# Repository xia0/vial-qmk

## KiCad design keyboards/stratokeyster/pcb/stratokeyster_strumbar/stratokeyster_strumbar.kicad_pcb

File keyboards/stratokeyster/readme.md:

# stratokeyster

## bom
|item|qty|
|---|---|
|M3 x 10~12 mm bolt*|16|
|M3 x 30 mm bolt*|4|
|M3 x 80 mm bolt|3|
|M3 nyloc nut|3|
|M3 heat set insert 5 mm OD x 4~5 mm L|20|
|M3 washer#|0~8|
|ec11 rotary encoder 15 mm half shaft|1|
|rs26 3 pole 4 throw rotary switch 15 mm half shaft|1|
|5 way pickup selector|1|
|passive buzzer 6.5 mm pin spacing|1|
|18 pin 2.54 mm pitch angled connector male^|1|
|18 pin 2.54 mm pitch dupont cable female end ~5 cm^|1|
|usb breakout board male|1|
|usb breakout board female|1|
|mx switch for fretboard|39-40|
|mx switch for bridge†|1|
|mx switch for strumbars†|6|
|2u pcb mount stab|2-3|
|2u plate mount stab|1|
|raspberry pi pico|1|
|fretboard pcb|1|
|fretboard plate|1|
|strumbar pcb|1|
|3d printed parts||

_\* phillips head silver colour bolts recommended for aesthetic reasons_\
_^ alternatively, a combination of pins that add up to 18_\
_# for tuning strum bar clearance. you could also use a 3d printed washer, bits of paper, etc..._\
_† heavy and clicky recommended e.g. kailh box navy or kailh box black_

## pick guard wiring
#### pickup selector
- com (4 or 5) -> row 3
- 1 or 6 -> col 8
- 2 or 7 -> col 7
- 3 or 8 -> col 6

#### EC11 rotary encoder
- push button -> row 3, col 9
- encoder -> encA, gnd, encB

encoder direction can be changed later on config layer

#### RS26 rotary switch
- A -> row 3
- 1 -> col 13
- 2 -> col 12
- 3 -> col 11
- 4 -> col 10

#### bridge key
row 1, col 13

#### buzzer
- +ve -> GP0
- -ve -> ground

#### free pin
row 2, col 13

## usage
#### pickup selector (mods) defaults
| neck | neck + mid | middle | bridge + mid | bridge |
|---|---|---|---|---|
| gui | ctrl + alt | alt | ctrl | none |

#### rotary encoder
- volume control
- mute/unmute

#### rotary switch
| pos 1 (ccw) | pos 2 | pos 3 | pos 4 (cw) |
|---|---|---|---|
| config | normal typing | strum typing | numbers |

#### bridge switch (palm mute)
does not hold down the key and does not register space if the key is released before the strum bar.

### config layer
the hid console in qmk toolbox can be useful to view which options are set but is not necessary.
|control|function|
|---|---|
|middle strum bar|toggle between simple mode and normal mode*|
|backslash|toggle between backslash or backspace|
|tab|toggle between tab or escape|
|bridge key|NUM layer replaces palm mute (quick access to high strings)|
|encoder push button|bootloader|
|encoder rotate|set direction of rotation as clockwise|
|a|toggle audio|
|d|toggle drop D tuning|
|r|reset eeprom|
|[|???|

_* in simple mode, only the middle strum bar is active._

#### edit mods
mods can be changed by selecting the pickup position, hold the desired mods and press enter to set.
|left shift|z|x|c|
|---|---|---|---|
|left shift|left ctrl|left gui|left alt|

switch off the config layer to save to eeprom.

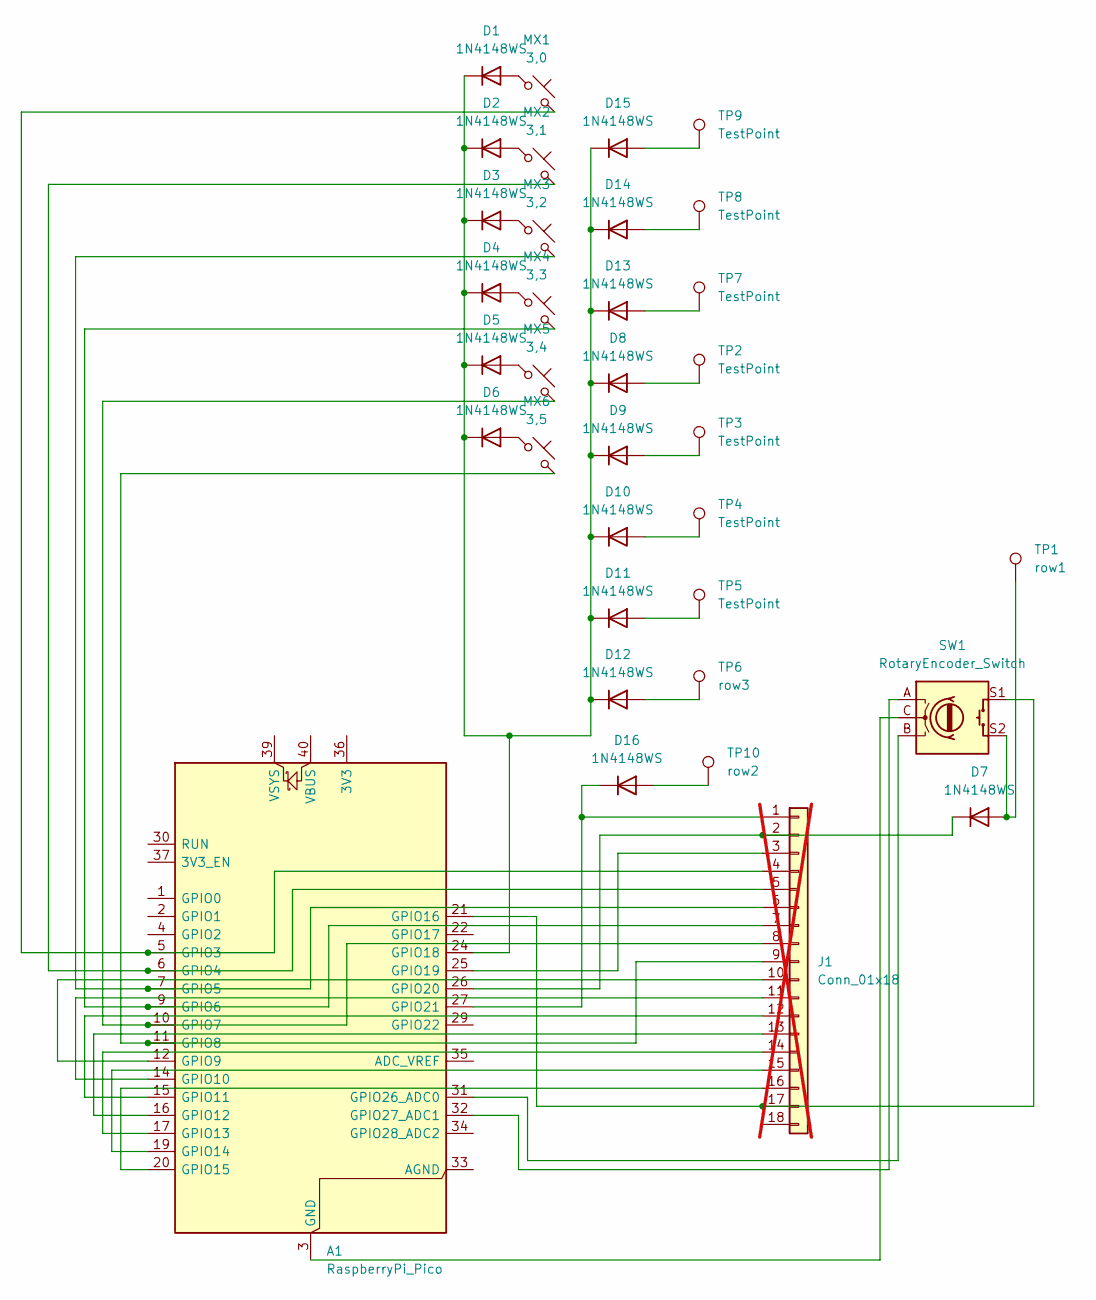
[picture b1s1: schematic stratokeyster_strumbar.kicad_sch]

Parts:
A1: RaspberryPi_Pico; RaspberryPi_Pico_Common_Unspecified
D1, D2, D3, D4, D5, D6, D7, D8, D9, D10, D11, D12, D13, D14, D15, D16: 1N4148WS; D_SOD-323_HandSoldering
J1: Conn_01x18; PinHeader_1x18_P2.54mm_Vertical; not fitted
MX1: 3,0; SW_MX_1u
MX2: 3,1; SW_MX_1u
MX3: 3,2; SW_MX_1u
MX4: 3,3; SW_MX_1u
MX5: 3,4; SW_MX_1u
MX6: 3,5; SW_MX_1u
SW1: RotaryEncoder_Switch
TP1: row1; TestPoint_Pad_1.5x1.5mm
TP2, TP3, TP4, TP5, TP7, TP8, TP9: TestPoint; TestPoint_Pad_1.5x1.5mm
TP6: row3; TestPoint_Pad_1.5x1.5mm
TP10: row2; TestPoint_Pad_1.5x1.5mm

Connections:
unnamed: A1.3 (GND), A1.8 (GND), A1.13 (GND), A1.18 (GND), A1.23 (GND), A1.28 (GND), A1.38 (GND), SW1.C
unnamed: A1.5 (GPIO3), J1.4, MX1.2
unnamed: A1.6 (GPIO4), J1.5, MX2.2
unnamed: A1.7 (GPIO5), J1.6, MX3.2
unnamed: A1.9 (GPIO6), J1.7, MX4.2
unnamed: A1.10 (GPIO7), J1.8, MX5.2
unnamed: A1.11 (GPIO8), J1.9, MX6.2
unnamed: A1.12 (GPIO9), J1.10
unnamed: A1.14 (GPIO10), J1.11
unnamed: A1.15 (GPIO11), J1.12
unnamed: A1.16 (GPIO12), J1.13
unnamed: A1.17 (GPIO13), J1.14
unnamed: A1.19 (GPIO14), J1.15
unnamed: A1.20 (GPIO15), J1.16
unnamed: A1.21 (GPIO16), J1.17, SW1.S1
unnamed: A1.24 (GPIO18), D1.1 (K), D2.1 (K), D3.1 (K), D4.1 (K), D5.1 (K), D6.1 (K), D8.1 (K), D9.1 (K), D10.1 (K), D11.1 (K), D12.1 (K), D13.1 (K), D14.1 (K), D15.1 (K)
unnamed: A1.25 (GPIO19), J1.3
unnamed: A1.26 (GPIO20), D7.1 (K), J1.2
unnamed: A1.27 (GPIO21), D16.1 (K), J1.1
unnamed: A1.31 (GPIO26_ADC0), SW1.B
unnamed: A1.32 (GPIO27_ADC1), SW1.A
unnamed: D1.2 (A), MX1.1
unnamed: D2.2 (A), MX2.1
unnamed: D3.2 (A), MX3.1
unnamed: D4.2 (A), MX4.1
unnamed: D5.2 (A), MX5.1
unnamed: D6.2 (A), MX6.1
unnamed: D7.2 (A), SW1.S2, TP1.1
unnamed: D8.2 (A), TP2.1
unnamed: D9.2 (A), TP3.1
unnamed: D10.2 (A), TP4.1
unnamed: D11.2 (A), TP5.1
unnamed: D12.2 (A), TP6.1
unnamed: D13.2 (A), TP7.1
unnamed: D14.2 (A), TP8.1
unnamed: D15.2 (A), TP9.1
unnamed: D16.2 (A), TP10.1

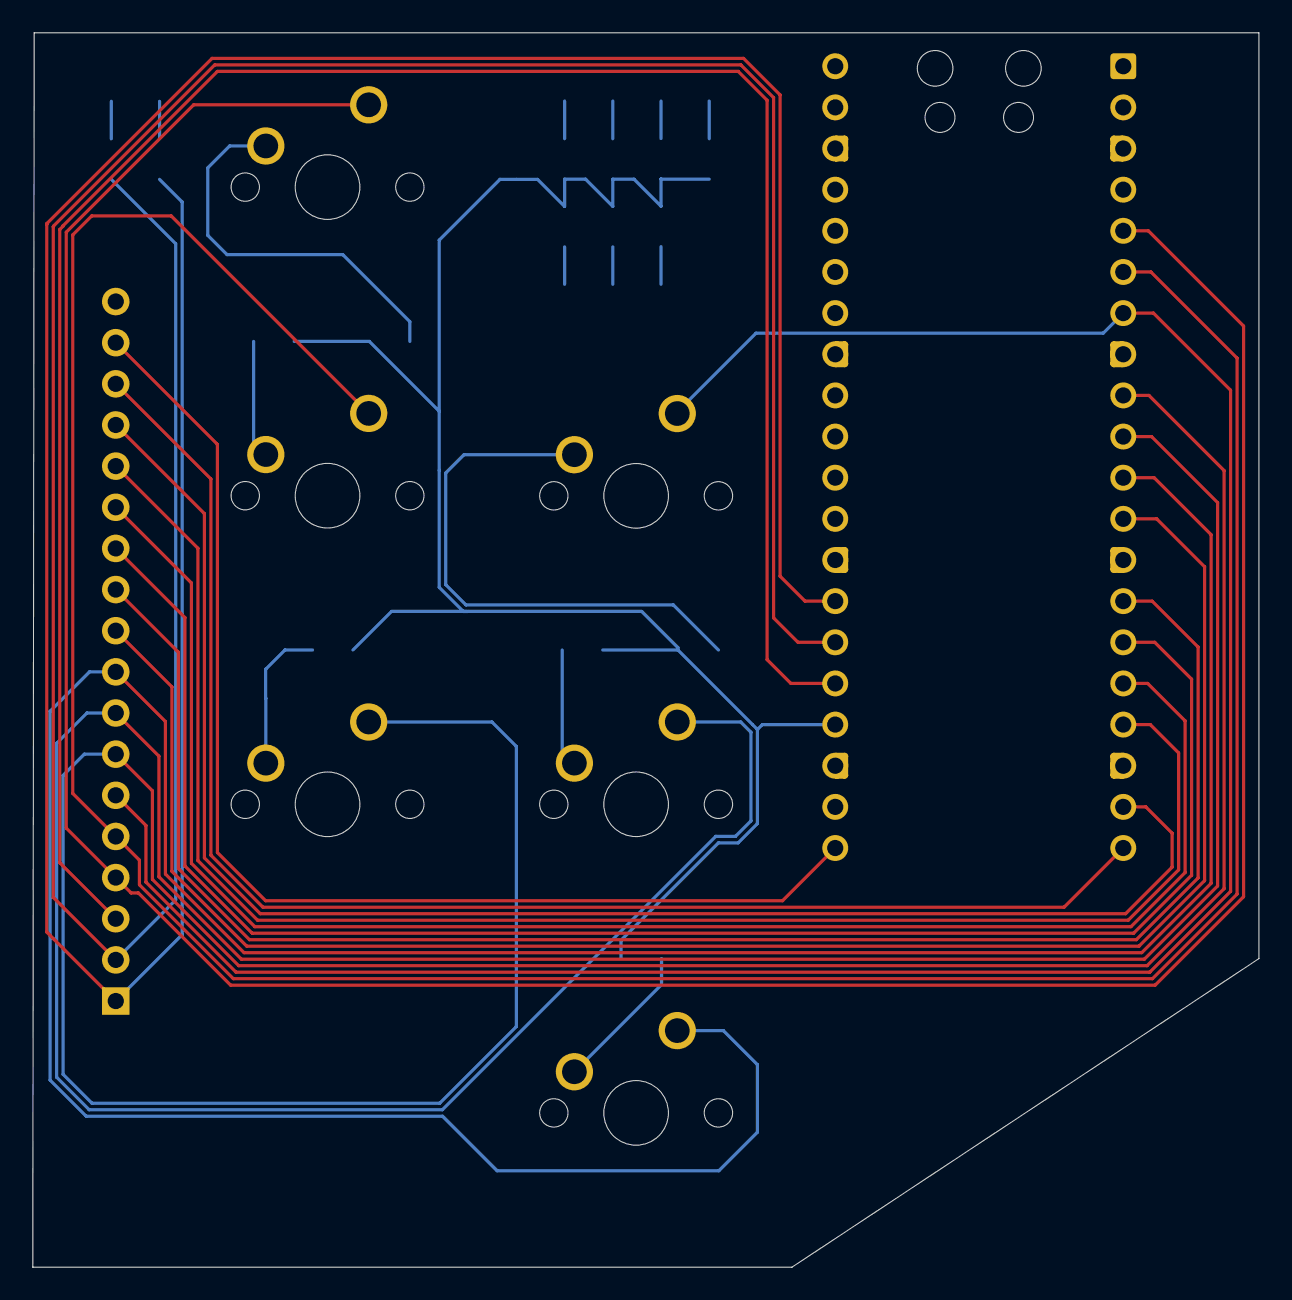
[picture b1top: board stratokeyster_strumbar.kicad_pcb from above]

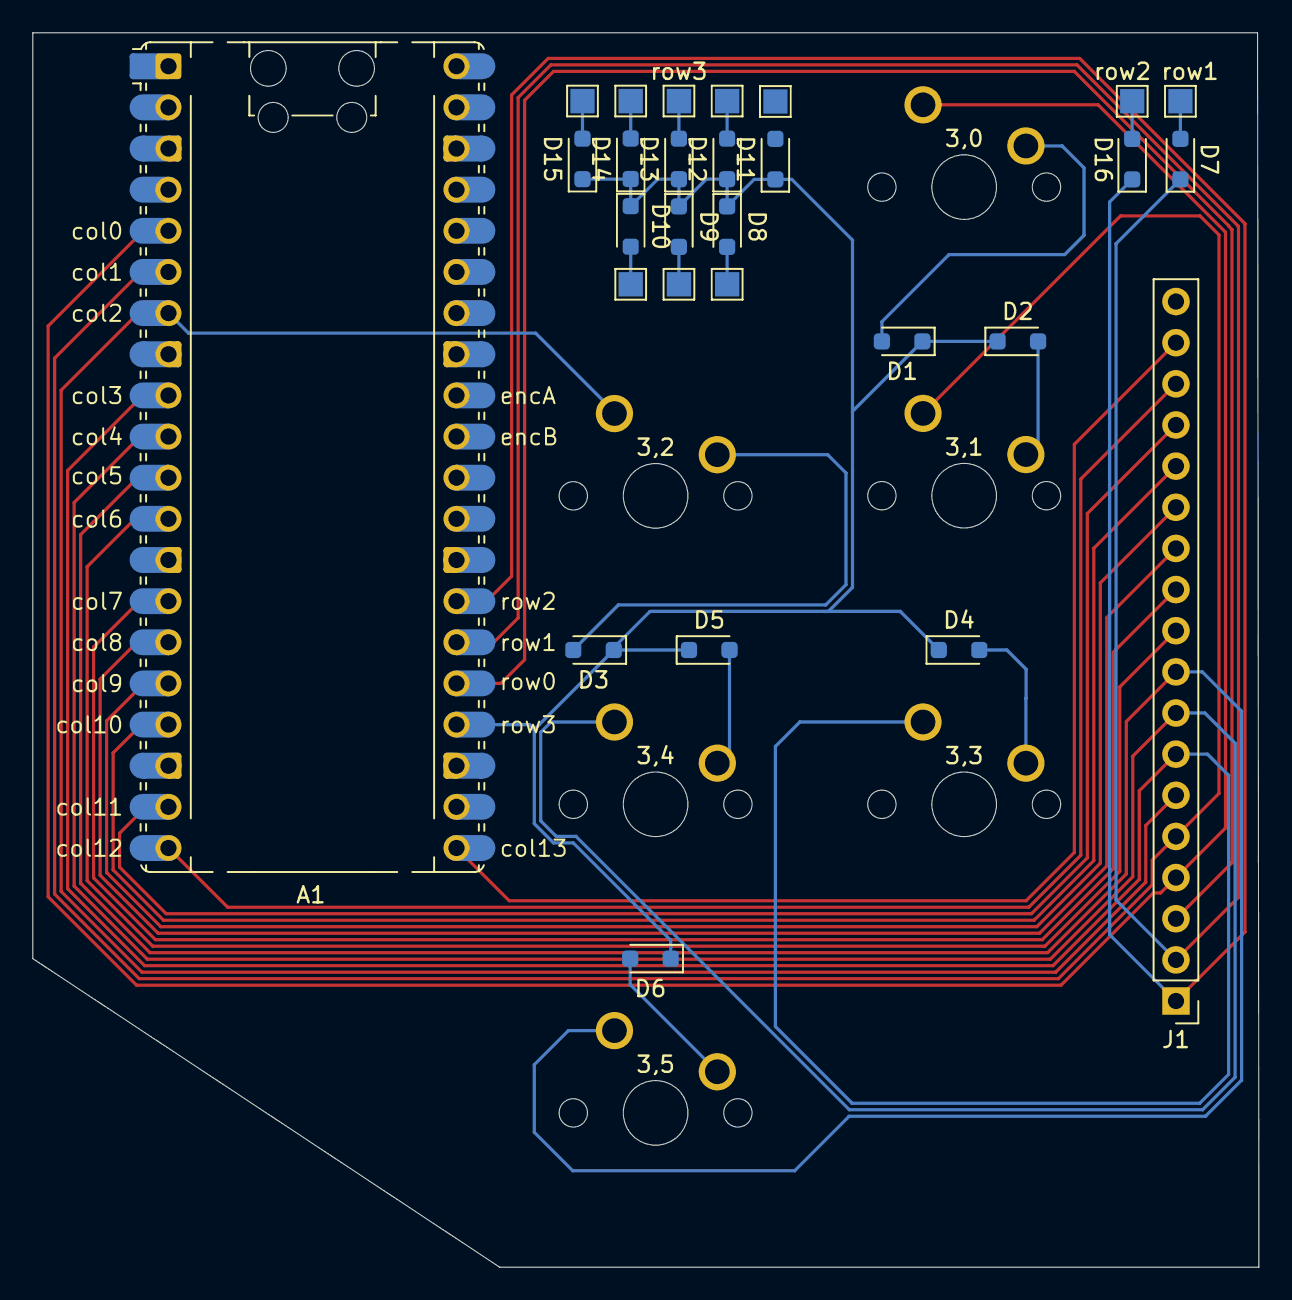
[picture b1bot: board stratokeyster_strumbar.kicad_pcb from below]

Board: 2 copper layers, 75.7 x 76.2 mm, 34 parts (28 on the bottom side), 35 nets.

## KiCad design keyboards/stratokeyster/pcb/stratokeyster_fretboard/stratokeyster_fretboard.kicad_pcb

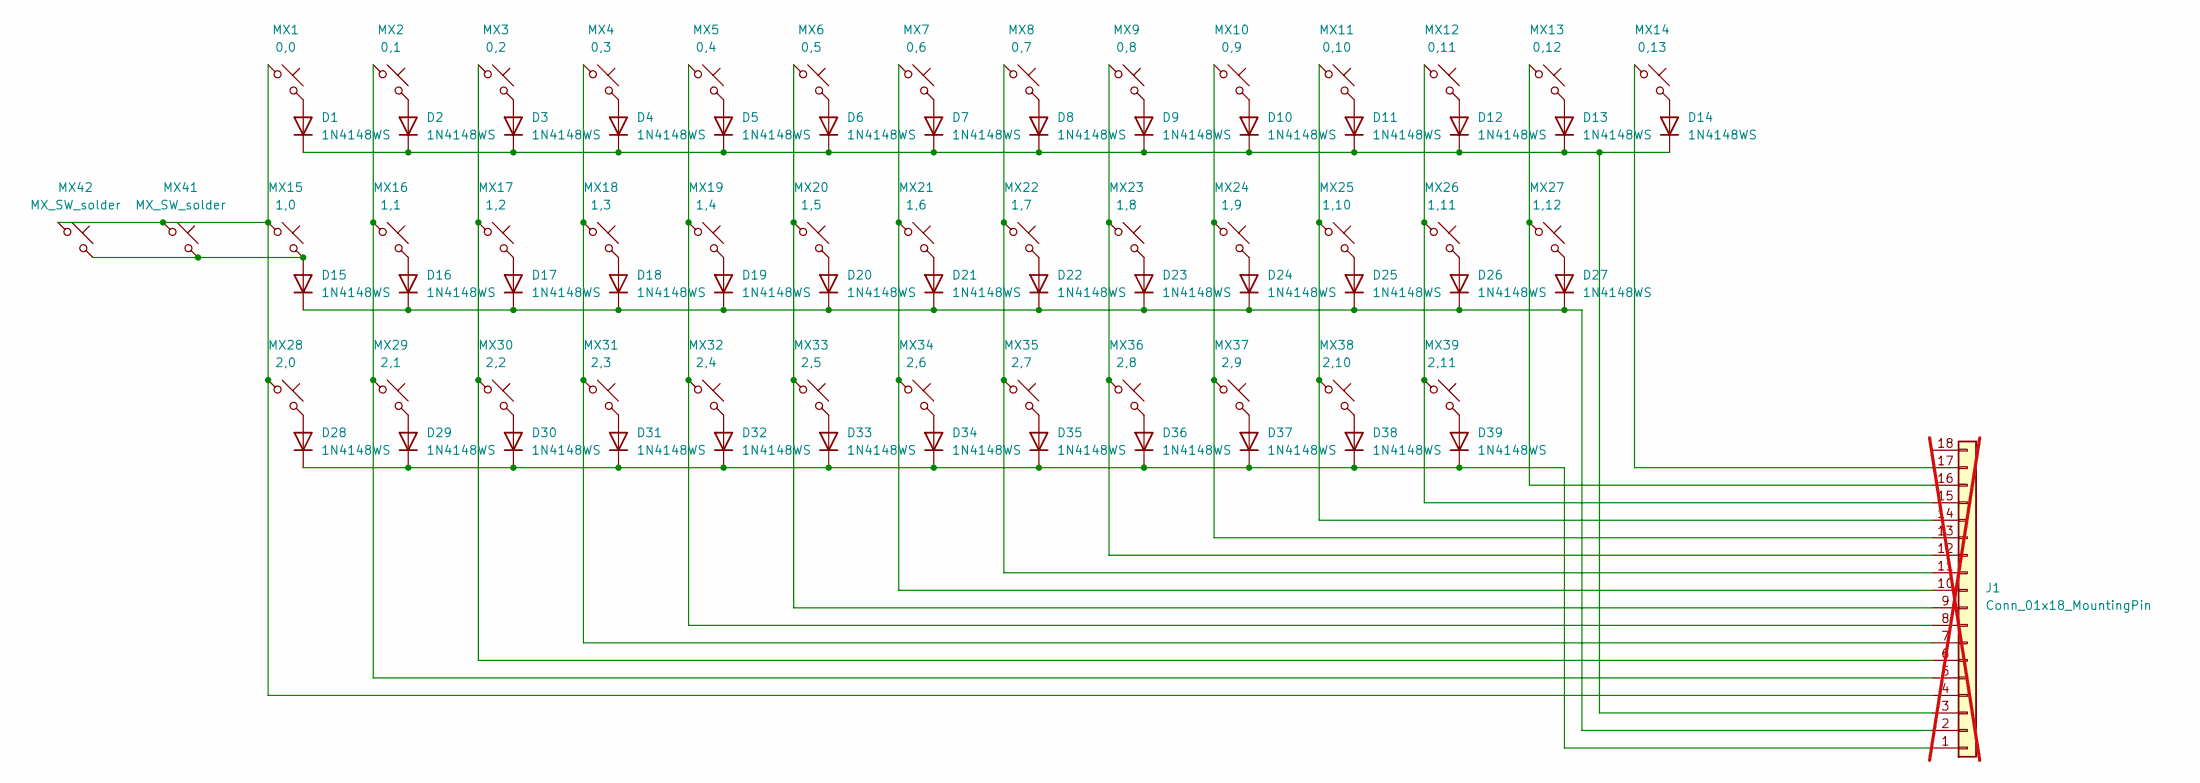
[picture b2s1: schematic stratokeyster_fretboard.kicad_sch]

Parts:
D1, D2, D3, D4, D5, D6, D7, D8, D9, D10, D11, D12, D13, D14, D15, D16, D17, D18, D19, D20, D21, D22, D23, D24, D25, D26, D27, D28, D29, D30, D31, D32, D33, D34, D35, D36, D37, D38, D39: 1N4148WS; D_SOD-323_HandSoldering
J1: Conn_01x18_MountingPin; PinHeader_1x18_P2.54mm_Horizontal; not fitted
MX1: 0,0; SW_MX_1.5u
MX2: 0,1; SW_MX_1u
MX3: 0,2; SW_MX_1u
MX4: 0,3; SW_MX_1u
MX5: 0,4; SW_MX_1u
MX6: 0,5; SW_MX_1u
MX7: 0,6; SW_MX_1u
MX8: 0,7; SW_MX_1u
MX9: 0,8; SW_MX_1u
MX10: 0,9; SW_MX_1u
MX11: 0,10; SW_MX_1u
MX12: 0,11; SW_MX_1u
MX13: 0,12; SW_MX_1u
MX14: 0,13; SW_MX_1.5u
MX15: 1,0; SW_MX_1.75u
MX16: 1,1; SW_MX_1u
MX17: 1,2; SW_MX_1u
MX18: 1,3; SW_MX_1u
MX19: 1,4; SW_MX_1u
MX20: 1,5; SW_MX_1u
MX21: 1,6; SW_MX_1u
MX22: 1,7; SW_MX_1u
MX23: 1,8; SW_MX_1u
MX24: 1,9; SW_MX_1u
MX25: 1,10; SW_MX_1u
MX26: 1,11; SW_MX_1u
MX27: 1,12; SW_MX_1u
MX28: 2,0; SW_MX_1u
MX29: 2,1; SW_MX_1u
MX30: 2,2; SW_MX_1u
MX31: 2,3; SW_MX_1u
MX32: 2,4; SW_MX_1u
MX33: 2,5; SW_MX_1u
MX34: 2,6; SW_MX_1u
MX35: 2,7; SW_MX_1u
MX36: 2,8; SW_MX_1u
MX37: 2,9; SW_MX_1u
MX38: 2,10; SW_MX_1u
MX39: 2,11; SW_MX_1u
MX41: MX_SW_solder; SW_MX_1.75u_STP_1.25
MX42: MX_SW_solder; SW_MX_1.75u_STP_1.5

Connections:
unnamed: D1.2 (A), MX1.2
unnamed: D1.1 (K), D2.1 (K), D3.1 (K), D4.1 (K), D5.1 (K), D6.1 (K), D7.1 (K), D8.1 (K), D9.1 (K), D10.1 (K), D11.1 (K), D12.1 (K), D13.1 (K), D14.1 (K), J1.3
unnamed: D2.2 (A), MX2.2
unnamed: D3.2 (A), MX3.2
unnamed: D4.2 (A), MX4.2
unnamed: D5.2 (A), MX5.2
unnamed: D6.2 (A), MX6.2
unnamed: D7.2 (A), MX7.2
unnamed: D8.2 (A), MX8.2
unnamed: D9.2 (A), MX9.2
unnamed: D10.2 (A), MX10.2
unnamed: D11.2 (A), MX11.2
unnamed: D12.2 (A), MX12.2
unnamed: D13.2 (A), MX13.2
unnamed: D14.2 (A), MX14.2
unnamed: D15.2 (A), MX15.2, MX41.2, MX42.2
unnamed: D15.1 (K), D16.1 (K), D17.1 (K), D18.1 (K), D19.1 (K), D20.1 (K), D21.1 (K), D22.1 (K), D23.1 (K), D24.1 (K), D25.1 (K), D26.1 (K), D27.1 (K), J1.2
unnamed: D16.2 (A), MX16.2
unnamed: D17.2 (A), MX17.2
unnamed: D18.2 (A), MX18.2
unnamed: D19.2 (A), MX19.2
unnamed: D20.2 (A), MX20.2
unnamed: D21.2 (A), MX21.2
unnamed: D22.2 (A), MX22.2
unnamed: D23.2 (A), MX23.2
unnamed: D24.2 (A), MX24.2
unnamed: D25.2 (A), MX25.2
unnamed: D26.2 (A), MX26.2
unnamed: D27.2 (A), MX27.2
unnamed: D28.2 (A), MX28.2
unnamed: D28.1 (K), D29.1 (K), D30.1 (K), D31.1 (K), D32.1 (K), D33.1 (K), D34.1 (K), D35.1 (K), D36.1 (K), D37.1 (K), D38.1 (K), D39.1 (K), J1.1
unnamed: D29.2 (A), MX29.2
unnamed: D30.2 (A), MX30.2
unnamed: D31.2 (A), MX31.2
unnamed: D32.2 (A), MX32.2
unnamed: D33.2 (A), MX33.2
unnamed: D34.2 (A), MX34.2
unnamed: D35.2 (A), MX35.2
unnamed: D36.2 (A), MX36.2
unnamed: D37.2 (A), MX37.2
unnamed: D38.2 (A), MX38.2
unnamed: D39.2 (A), MX39.2
unnamed: J1.4, MX1.1, MX15.1, MX28.1, MX41.1, MX42.1
unnamed: J1.5, MX2.1, MX16.1, MX29.1
unnamed: J1.6, MX3.1, MX17.1, MX30.1
unnamed: J1.7, MX4.1, MX18.1, MX31.1
unnamed: J1.8, MX5.1, MX19.1, MX32.1
unnamed: J1.9, MX6.1, MX20.1, MX33.1
unnamed: J1.10, MX7.1, MX21.1, MX34.1
unnamed: J1.11, MX8.1, MX22.1, MX35.1
unnamed: J1.12, MX9.1, MX23.1, MX36.1
unnamed: J1.13, MX10.1, MX24.1, MX37.1
unnamed: J1.14, MX11.1, MX25.1, MX38.1
unnamed: J1.15, MX12.1, MX26.1, MX39.1
unnamed: J1.16, MX13.1, MX27.1
unnamed: J1.17, MX14.1

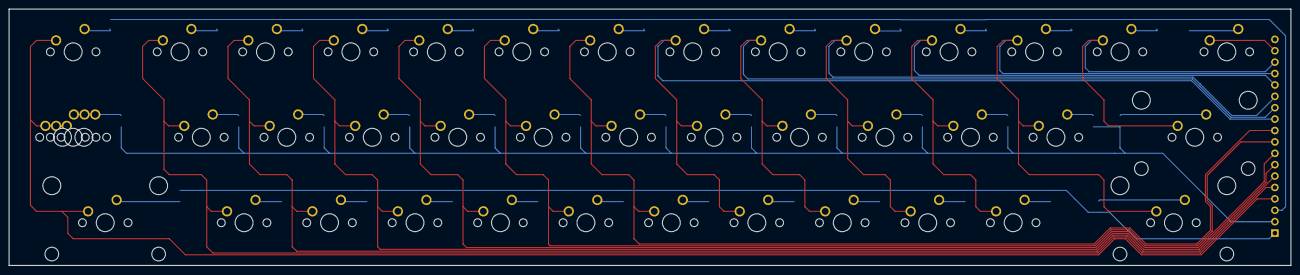
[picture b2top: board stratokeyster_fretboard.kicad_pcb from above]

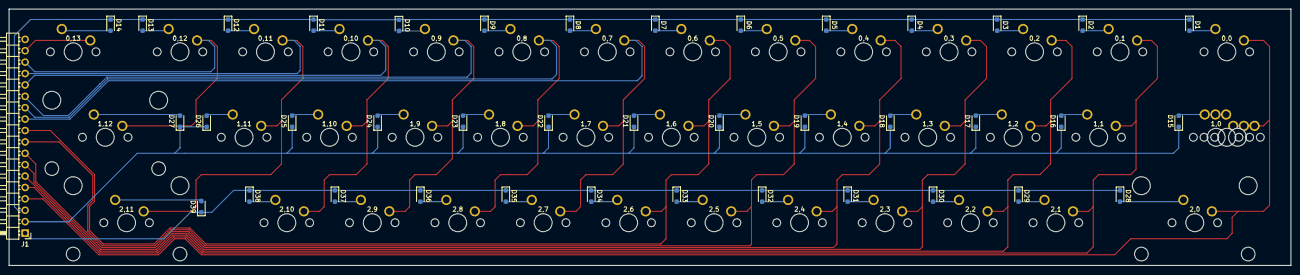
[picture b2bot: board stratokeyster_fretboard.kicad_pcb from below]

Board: 2 copper layers, 285.8 x 57.1 mm, 81 parts (40 on the bottom side), 56 nets.

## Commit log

2023-04-23 added vial keymap for 3dp660 oled
2023-04-26 Changed OLED idle time
2023-04-30 Fixed incorrect matrix for unlocking bootloader
2024-09-27 updated json definitions for rp2040 gpio pins
2024-09-28 fixed mixed up order of L/R and U/D for encoders on layer 1
2026-01-28 added stratokeyster
2026-01-28 fixed matrix def
2026-01-28 changing keymap
2026-01-28 fixing matrix
2026-01-28 fixing keymap
2026-01-28 reverted some unrelated files
2026-01-28 added kicad files
2026-01-28 Revert "added kicad files"
    This reverts commit d4a971190be737d1a7d485250e5be473c7dc2990.
2026-03-27 fixed a bunch of shit
2026-03-27 changed pickup mods
2026-03-29 trying to figure out mods
2026-04-02 fixing logic for hammer ons and pull offs
2026-04-03 revising hammer on logic
2026-04-03 fixed missing comma in layout
2026-04-03 tidy some remarks
2026-04-05 added ability to toggle backslash as backspace
2026-04-06 added config options for mods, backspace, esc
2026-04-07 changed eeprom driver back to rp2040
2026-04-07 added number layer and logic for it
2026-04-07 added easter egg
2026-04-07 fixed minor bugs
2026-04-07 fixed ability to use number layer in normal typing
2026-04-08 added option to reverse encoder direction. fixed logic checking out of fretboard keys.
2026-04-08 do not play space on fret release if palm muted
2026-04-13 added pics
2026-04-13 resize image
2026-04-17 Added audio functionality
2026-04-19 fixed some logic with audio
2026-04-19 added option to change bridge key to access high 3 strings
2026-05-24 port to vial
2026-06-17 changed rules to not wait for usb enumeration
